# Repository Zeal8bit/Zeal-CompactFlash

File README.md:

## CompactFlash adapter for Zeal 8-bit Computer

<center>
    
</center>

## This repository is part of [this Youtube video](https://youtu.be/B_ADYc3EVzc), check it for more information and explanation about this project.

The goal of this project is to create an adapter for connecting CompactFlash cards to Zeal 8-bit Computer.

This repository includes:

* An example/driver written in Z80 assembly to communicate with the adapter. It will read the first sector (512 bytes) of the card, show the first two 16-byte line, invert them and write the result back in the CompactFlash. Both 16-byte lines will be printed on screen.
* A Kicad project for the schematics and PCB board

The output of the example on Zeal 8-bit OS should look like this:

<center>
    
</center>

## About the connector

<s>As described in [the Youtube video](https://youtu.be/B_ADYc3EVzc), the CompactFlash connector needs to accept cards inserted bottom up. This is because the footprint of the connector is mirrored on the PCB.</s>

**Update v1.0.0:** the PCB and its connector have been fixed, the card can be connected upside up.

## Requirements

To compile this example you will need:
* bash
* git (to clone this repo)
* make
* Zeal 8-bit OS source code. Only the kernel_headers directory is required, check [this repository](https://github.com/Zeal8bit/Zeal-8-bit-OS).
* z88dk v2.2 (or later). Only its assembler, z80asm, is strictly required. The latest version of z80asm must be used as earlier versions don't have support for MACRO.

To install z88dk, please check out their Github project.

## Build

To build the program, define the path to Zeal 8-bit OS, this will let us find the header files used to assemble the example:

```
export ZOS_PATH=/your/path/to/Zeal8bitOS
```

Then simply use the command:

```
make
```

After compiling, the folder `bin/` should contain the binary `readcf.bin`. This file can be then loaded to Zeal 8-bit OS through UART thanks to the `load` command.

The binary can also be embedded within the romdisk that will contain both the OS and a read-only file system. For example:

```
cd $ZOS_PATH
export EXTRA_ROMDISK_FILES="/path/to/this/repo/bin/readcf.bin"
make
```
More info about compiling Zeal 8-bit OS [here](https://github.com/Zeal8bit/Zeal-8-bit-OS#getting-started).

The resulted ROM image can then be provided to an emulator or directly flashed to the computer's ROM that will use it.

## License

Distributed under the Creative Commons Zero v1.0 Universal License. See LICENSE file for more information.

You are free to use it for personal and commercial use, the boilerplate present in each file must not be removed.

## Contact

For any suggestion or request, you can contact me at contact [at] zeal8bit [dot] com or on the Discord server https://discord.gg/UzEjwRvBBb

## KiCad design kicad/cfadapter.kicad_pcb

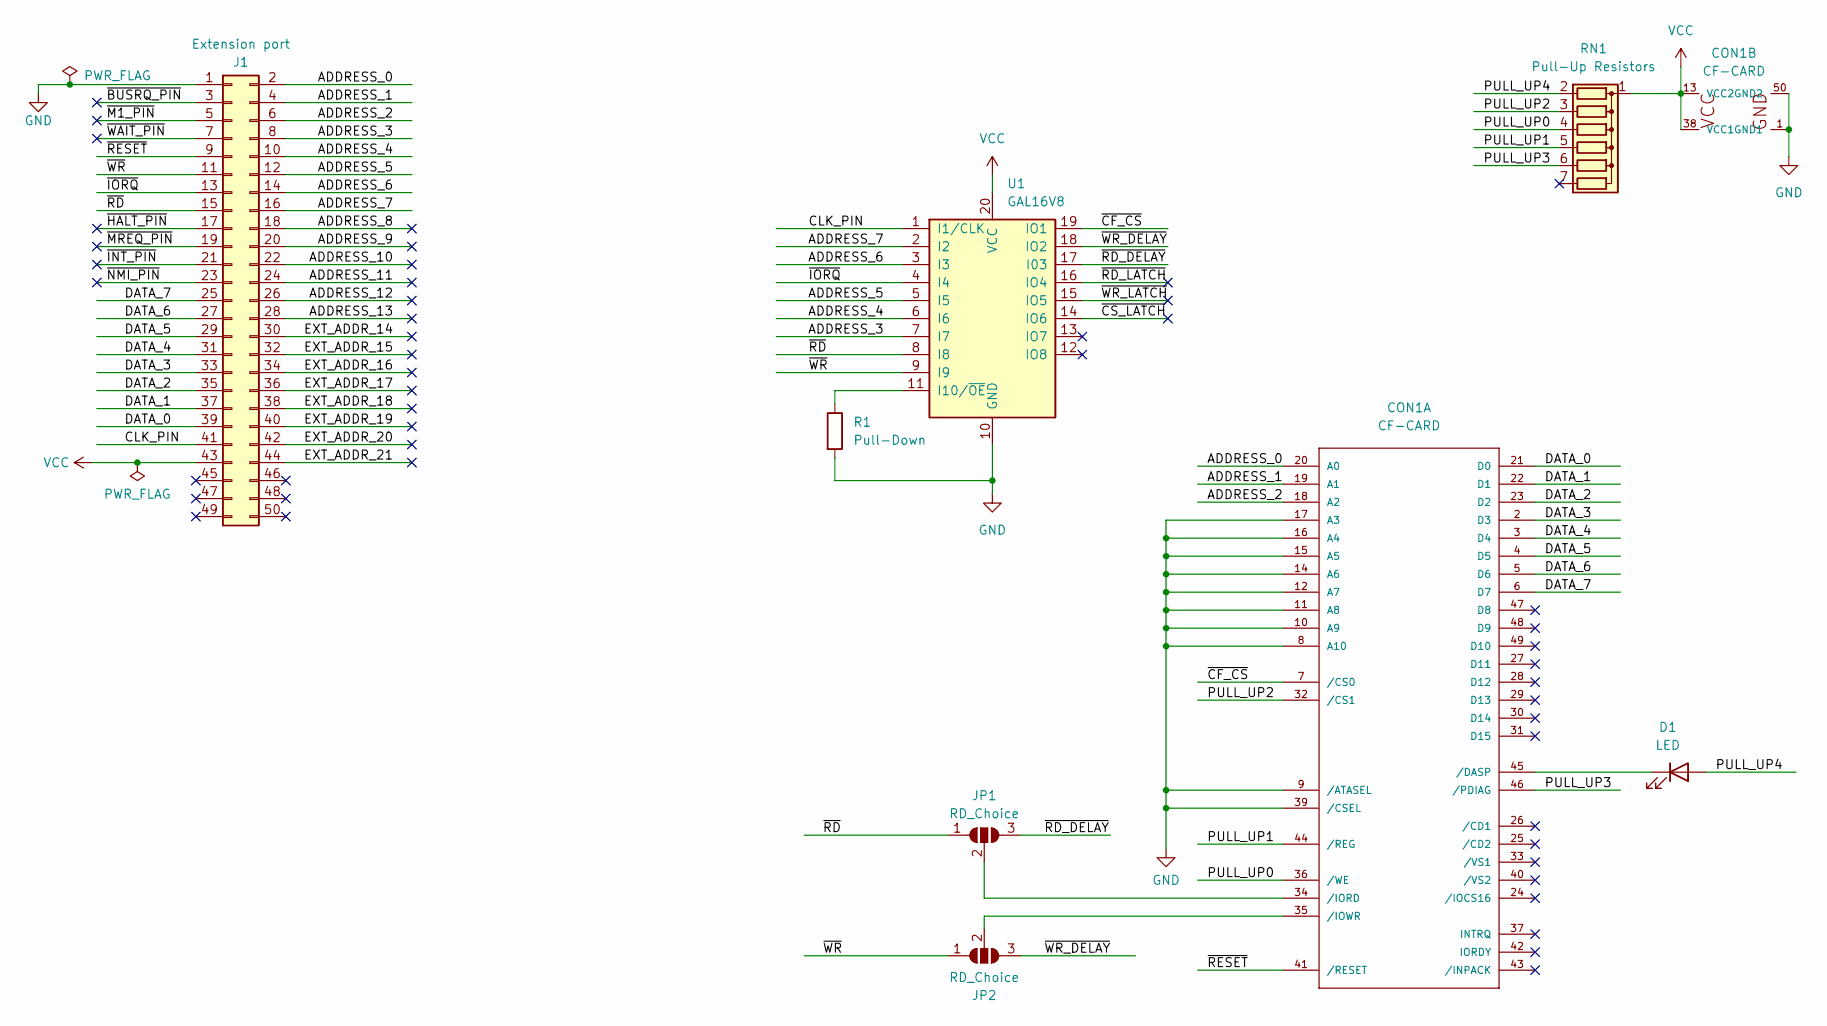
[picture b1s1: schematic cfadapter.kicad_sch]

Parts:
CON1: CF-CARD; CF-Card_3M_N7E50-E516xx-30
D1: LED; LED_D5.0mm
J1: Extension port; PinHeader_2x25_P2.54mm_Vertical
JP1, JP2: RD_Choice; SolderJumper-3_P2.0mm_Open_TrianglePad1.0x1.5mm_NumberLabels
R1: Pull-Down; R_Axial_DIN0207_L6.3mm_D2.5mm_P10.16mm_Horizontal
RN1: Pull-Up Resistors; R_Array_SIP7
U1: GAL16V8; DIP-20_W7.62mm_Socket

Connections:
/ADDRESS_0: CON1.20 (A0), J1.2
/ADDRESS_1: CON1.19 (A1), J1.4
/ADDRESS_2: CON1.18 (A2), J1.6
/ADDRESS_3: J1.8, U1.7 (I7)
/ADDRESS_4: J1.10, U1.6 (I6)
/ADDRESS_5: J1.12, U1.5 (I5)
/ADDRESS_6: J1.14, U1.3 (I3)
/ADDRESS_7: J1.16, U1.2 (I2)
/ADDRESS_8: J1.18
/ADDRESS_9: J1.20
/ADDRESS_10: J1.22
/ADDRESS_11: J1.24
/ADDRESS_12: J1.26
/ADDRESS_13: J1.28
/CLK_PIN: J1.41, U1.1 (I1/CLK)
/DATA_0: CON1.21 (D0), J1.39
/DATA_1: CON1.22 (D1), J1.37
/DATA_2: CON1.23 (D2), J1.35
/DATA_3: CON1.2 (D3), J1.33
/DATA_4: CON1.3 (D4), J1.31
/DATA_5: CON1.4 (D5), J1.29
/DATA_6: CON1.5 (D6), J1.27
/DATA_7: CON1.6 (D7), J1.25
/EXT_ADDR_14: J1.30
/EXT_ADDR_15: J1.32
/EXT_ADDR_16: J1.34
/EXT_ADDR_17: J1.36
/EXT_ADDR_18: J1.38
/EXT_ADDR_19: J1.40
/EXT_ADDR_20: J1.42
/EXT_ADDR_21: J1.44
/PULL_UP0: CON1.36 (/WE), RN1.4 (R3)
/PULL_UP1: CON1.44 (/REG), RN1.5 (R4)
/PULL_UP2: CON1.32 (/CS1), RN1.3 (R2)
/PULL_UP3: CON1.46 (/PDIAG), RN1.6 (R5)
/PULL_UP4: D1.2 (A), RN1.2 (R1)
/~BUSRQ_PIN: J1.3
/~CF_CS: CON1.7 (/CS0), U1.19 (IO1)
/~CS_LATCH: U1.14 (IO6)
/~HALT_PIN: J1.17
/~INT_PIN: J1.21
/~IORQ: J1.13, U1.4 (I4)
/~M1_PIN: J1.5
/~MREQ_PIN: J1.19
/~NMI_PIN: J1.23
/~RD_DELAY: JP1.3 (B), U1.17 (I03)
/~RD_LATCH: U1.16 (IO4)
/~RD: J1.15, JP1.1 (A), U1.8 (I8)
/~RESET: CON1.41 (/RESET), J1.9
/~WAIT_PIN: J1.7
/~WR_DELAY: JP2.3 (B), U1.18 (IO2)
/~WR_LATCH: U1.15 (IO5)
/~WR: J1.11, JP2.1 (A), U1.9 (I9)
GND: CON1.1 (GND1), CON1.8 (A10), CON1.9 (/ATASEL), CON1.10 (A9), CON1.11 (A8), CON1.12 (A7), CON1.14 (A6), CON1.15 (A5), CON1.16 (A4), CON1.17 (A3), CON1.39 (/CSEL), CON1.50 (GND2), J1.1, R1.2, U1.10 (GND)
unnamed: CON1.45 (/DASP), D1.1 (K)
unnamed: CON1.34 (/IORD), JP1.2 (C)
unnamed: CON1.35 (/IOWR), JP2.2 (C)
unnamed: R1.1, U1.11 (I10/~OE)
VCC: CON1.13 (VCC2), CON1.38 (VCC1), J1.43, RN1.1 (common), U1.20 (VCC)

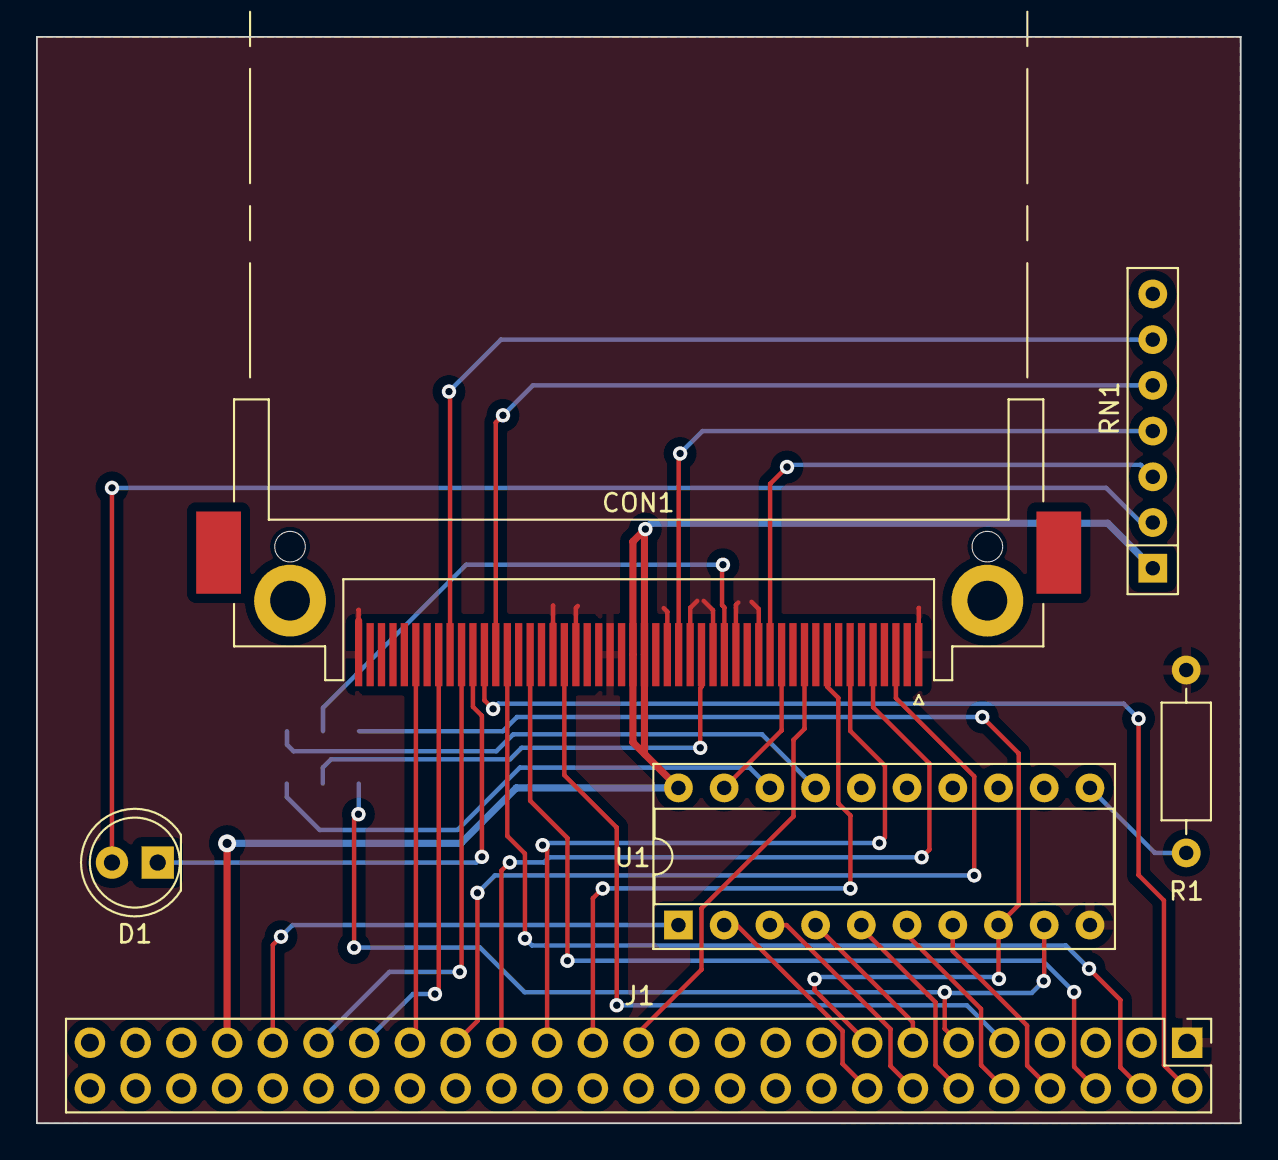
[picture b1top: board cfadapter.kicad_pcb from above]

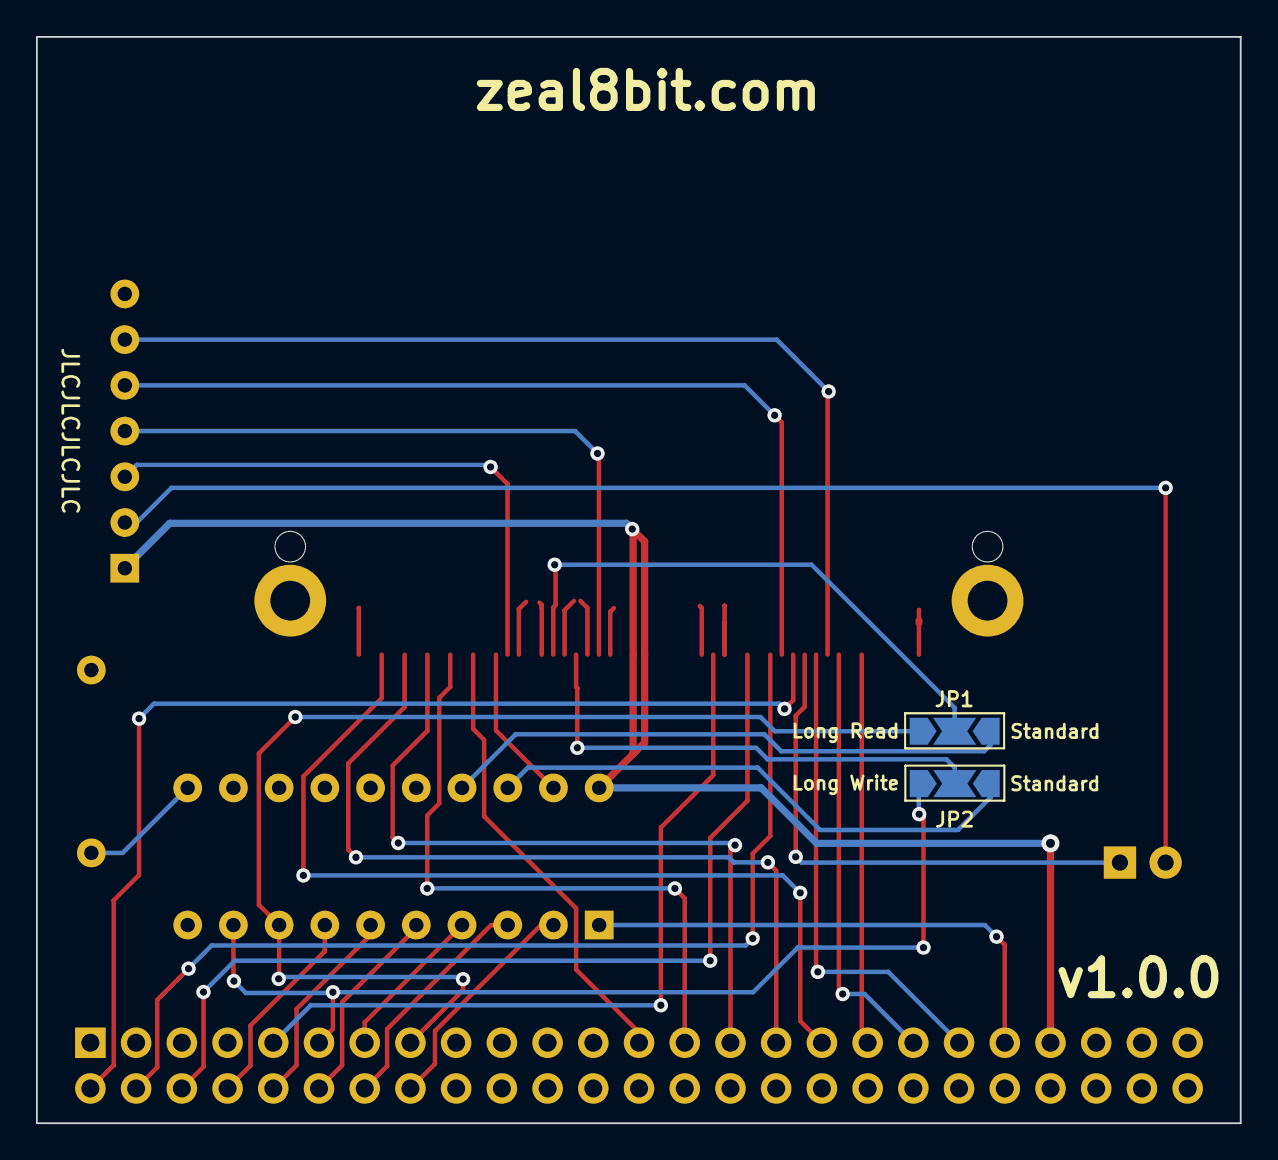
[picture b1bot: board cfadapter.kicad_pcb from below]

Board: 2 copper layers, 66.9 x 60.4 mm, 8 parts (2 on the bottom side), 35 nets.

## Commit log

2023-05-28 Publish program source code to read CompactFlash first sector on Zeal 8-bit Computer, as well as schematics and PCB designed in Kicad v6
2024-02-04 src/main.asm: Fix the example to properly read and write the CompactFlash
2024-02-04 kicad: Update the PCB to the manufactured v1.0.0
2024-02-04 README: Update the content to reflect the changes on the v1.0.0
2025-06-28 pld: add the file to flash to the 16V8 logic chip
2025-07-06 deassert CS later to meet CFA hold time specification
